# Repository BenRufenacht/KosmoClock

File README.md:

# KosmoClock
 Kosmo Format Clock Module based on LittleBen by Quinie 

Note that the UI varies significantly from Quinie's version.

Status:   
February 2023 - First run of manufacturing found some minor mistakes that were fixed, but the updates to the main board have not been tested.

License:  
[CC-BY-SA](https://creativecommons.org/licenses/by-sa/3.0/)

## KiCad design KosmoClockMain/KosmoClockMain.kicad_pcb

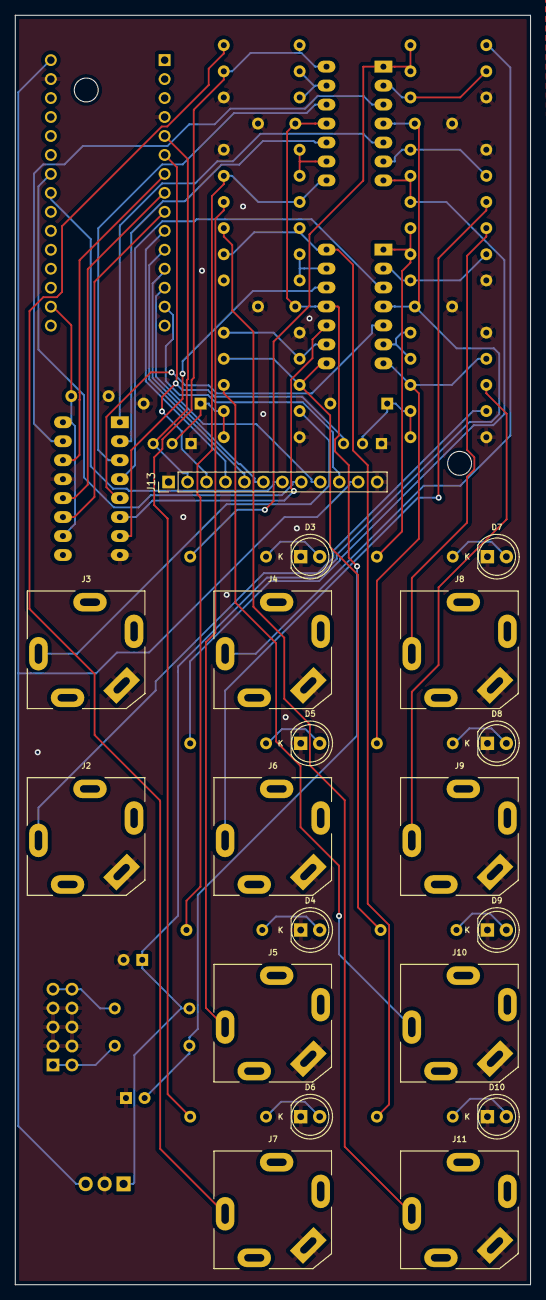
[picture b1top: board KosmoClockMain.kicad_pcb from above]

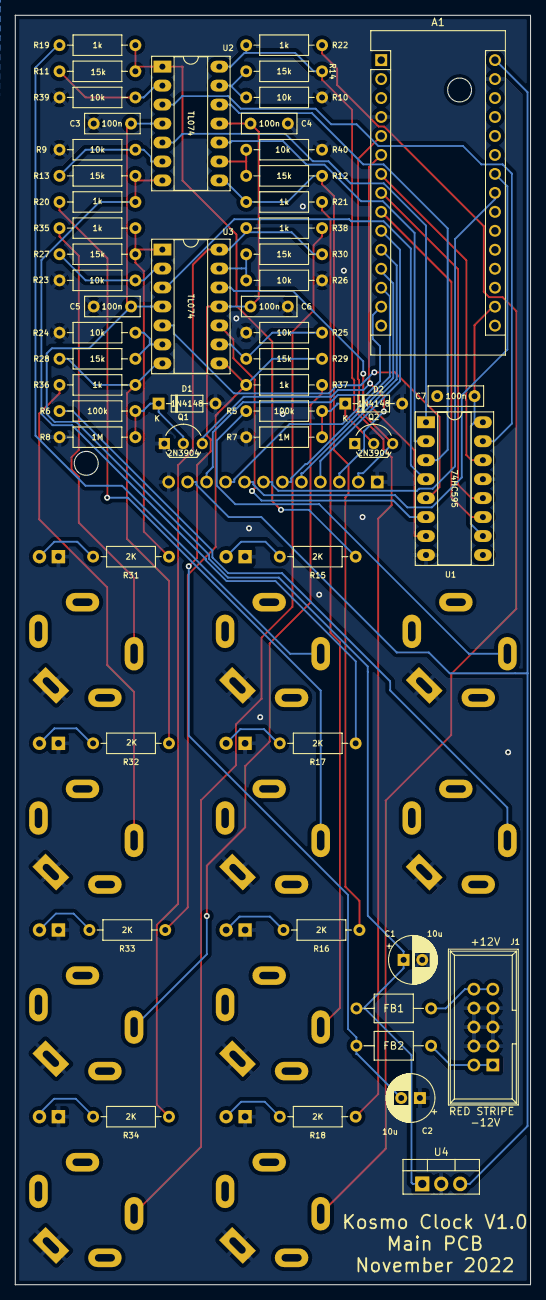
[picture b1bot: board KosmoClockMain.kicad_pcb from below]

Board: 2 copper layers, 69.0 x 170.0 mm, 74 parts (55 on the bottom side), 63 nets.

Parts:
A1: Arduino_Nano_v3.x; Arduino_Nano
C1, C2: 10u; CP_Radial_D6.3mm_P2.50mm
C3, C4, C5, C6, C7: 100n; C_Rect_L7.2mm_W2.5mm_P5.00mm_FKS2_FKP2_MKS2_MKP2
D1, D2: 1N4148; D_DO-35_SOD27_P7.62mm_Horizontal
D3, D4, D5, D6, D7, D8, D9, D10: LED_green; LED_D5.0mm
FB1, FB2: FerriteBead; L_Axial_L5.0mm_D3.6mm_P10.00mm_Horizontal_Murata_BL01RN1A2A2
J1: Synth_power_2x5_passive; Power_Header
J2, J3, J4, J5, J6, J7, J8, J9, J10, J11: AudioJack2; Jack_6.35mm_PJ_629HAN_slots
J13: Conn_01x12; PinHeader_1x12_P2.54mm_Vertical
Q1, Q2: 2N3904; TO-92_Inline_Wide
R5, R6: 100k; R_Axial_DIN0207_L6.3mm_D2.5mm_P10.16mm_Horizontal
R7, R8: 1M; R_Axial_DIN0207_L6.3mm_D2.5mm_P10.16mm_Horizontal
R9, R10, R23, R24, R25, R26, R39, R40: 10k; R_Axial_DIN0207_L6.3mm_D2.5mm_P10.16mm_Horizontal
R11, R12, R13, R14, R27, R28, R29, R30: 15k; R_Axial_DIN0207_L6.3mm_D2.5mm_P10.16mm_Horizontal
R15, R16, R17, R18, R31, R32, R33, R34: 2K; R_Axial_DIN0207_L6.3mm_D2.5mm_P10.16mm_Horizontal
R19, R20, R21, R22, R35, R36, R37, R38: 1k; R_Axial_DIN0207_L6.3mm_D2.5mm_P10.16mm_Horizontal
U1: 74HC595; DIP-16_W7.62mm_Socket_LongPads
U2, U3: TL074; DIP-14_W7.62mm_Socket_LongPads
U4: LM7805_TO220; TO-220-3_Vertical

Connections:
+3V3: A1.17 (3V3), C7.2, U1.10 (~SRCLR), U1.16 (VCC)
+5V: A1.30 (VIN), J13.11, U4.3 (VO)
+12V: C1.1, C3.1, C5.1, FB1.2, U2.4 (V+), U3.4 (V+), U4.1 (VI)
-12V: C2.2, C4.1, C6.1, FB2.2, U2.11 (V-), U3.11 (V-)
/CLOCK: A1.9 (D6), U1.11 (SRCLK)
/DATA: A1.7 (D4), U1.14 (SER)
/ENCA: A1.11 (D8), J13.5
/ENCB: A1.12 (D9), J13.6
/ENCS: A1.10 (D7), J13.4
/LATCH: A1.8 (D5), U1.12 (RCLK)
/OUT1: U1.15 (QA), U2.3 (+)
/OUT2: U1.1 (QB), U2.5 (+)
/OUT3: U1.2 (QC), U2.10 (+)
/OUT4: U1.3 (QD), U2.12 (+)
/OUT5: U1.4 (QE), U3.3 (+)
/OUT6: U1.5 (QF), U3.5 (+)
/OUT7: U1.6 (QG), U3.10 (+)
/OUT8: U1.7 (QH), U3.12 (+)
/SCL: A1.24 (A5), J13.8
/SDA: A1.23 (A4), J13.7
/START: A1.5 (D2), J13.2, Q2.3 (C)
/STARTLED: A1.13 (D10), J13.9
/STOP: A1.6 (D3), J13.3, Q1.3 (C)
/STOPLED: A1.14 (D11), J13.10
GND: A1.4 (GND), A1.29 (GND), C1.2, C2.1, C3.2, C4.2, C5.2, C6.2, C7.1, D1.2 (A), D2.2 (A), D3.1 (K), D4.1 (K), D5.1 (K), D6.1 (K), D7.1 (K), D8.1 (K), D9.1 (K), D10.1 (K), J1.3 (GND), J1.4 (GND), J1.5 (GND), J1.6 (GND), J1.7 (GND), J1.8 (GND), J2.S, J3.S, J4.S, J5.S, J6.S, J7.S, J8.S, J9.S, J10.S, J11.S, J13.1, J13.12, Q1.1 (E), Q2.1 (E), R7.2, R8.2, R9.1, R10.1, R23.1, R24.1, R25.1, R26.1, R39.1, R40.1, U1.8 (GND), U1.13 (~OE), U4.2 (GND)
unnamed: D1.1 (K), Q1.2 (B), R6.2, R8.1
unnamed: D2.1 (K), Q2.2 (B), R5.2, R7.1
unnamed: D3.2 (A), R15.2
unnamed: D4.2 (A), R16.2
unnamed: D5.2 (A), R17.2
unnamed: D6.2 (A), R18.2
unnamed: D7.2 (A), R31.2
unnamed: D8.2 (A), R32.2
unnamed: D9.2 (A), R33.2
unnamed: D10.2 (A), R34.2
unnamed: FB1.1, J1.9 (+12V), J1.10 (+12V)
unnamed: FB2.1, J1.1 (-12V), J1.2 (-12V)
unnamed: J2.T, R6.1
unnamed: J3.T, R5.1
unnamed: J4.T, R19.2
unnamed: J5.T, R21.2
unnamed: J6.T, R20.2
unnamed: J7.T, R22.2
unnamed: J8.T, R35.2
unnamed: J9.T, R36.2
unnamed: J10.T, R37.2
unnamed: J11.T, R38.2
unnamed: R10.2, R14.1, U2.13 (-)
unnamed: R11.1, R39.2, U2.2 (-)
unnamed: R11.2, R15.1, R19.1, U2.1
unnamed: R12.1, R40.2, U2.9 (-)
unnamed: R12.2, R16.1, R21.1, U2.8
unnamed: R9.2, R13.1, U2.6 (-)
unnamed: R13.2, R17.1, R20.1, U2.7
unnamed: R14.2, R18.1, R22.1, U2.14
unnamed: R23.2, R27.1, U3.2 (-)
unnamed: R24.2, R28.1, U3.6 (-)
unnamed: R25.2, R29.1, U3.9 (-)
unnamed: R26.2, R30.1, U3.13 (-)
unnamed: R27.2, R31.1, R35.1, U3.1
unnamed: R28.2, R32.1, R36.1, U3.7
unnamed: R29.2, R33.1, R37.1, U3.8
unnamed: R30.2, R34.1, R38.1, U3.14

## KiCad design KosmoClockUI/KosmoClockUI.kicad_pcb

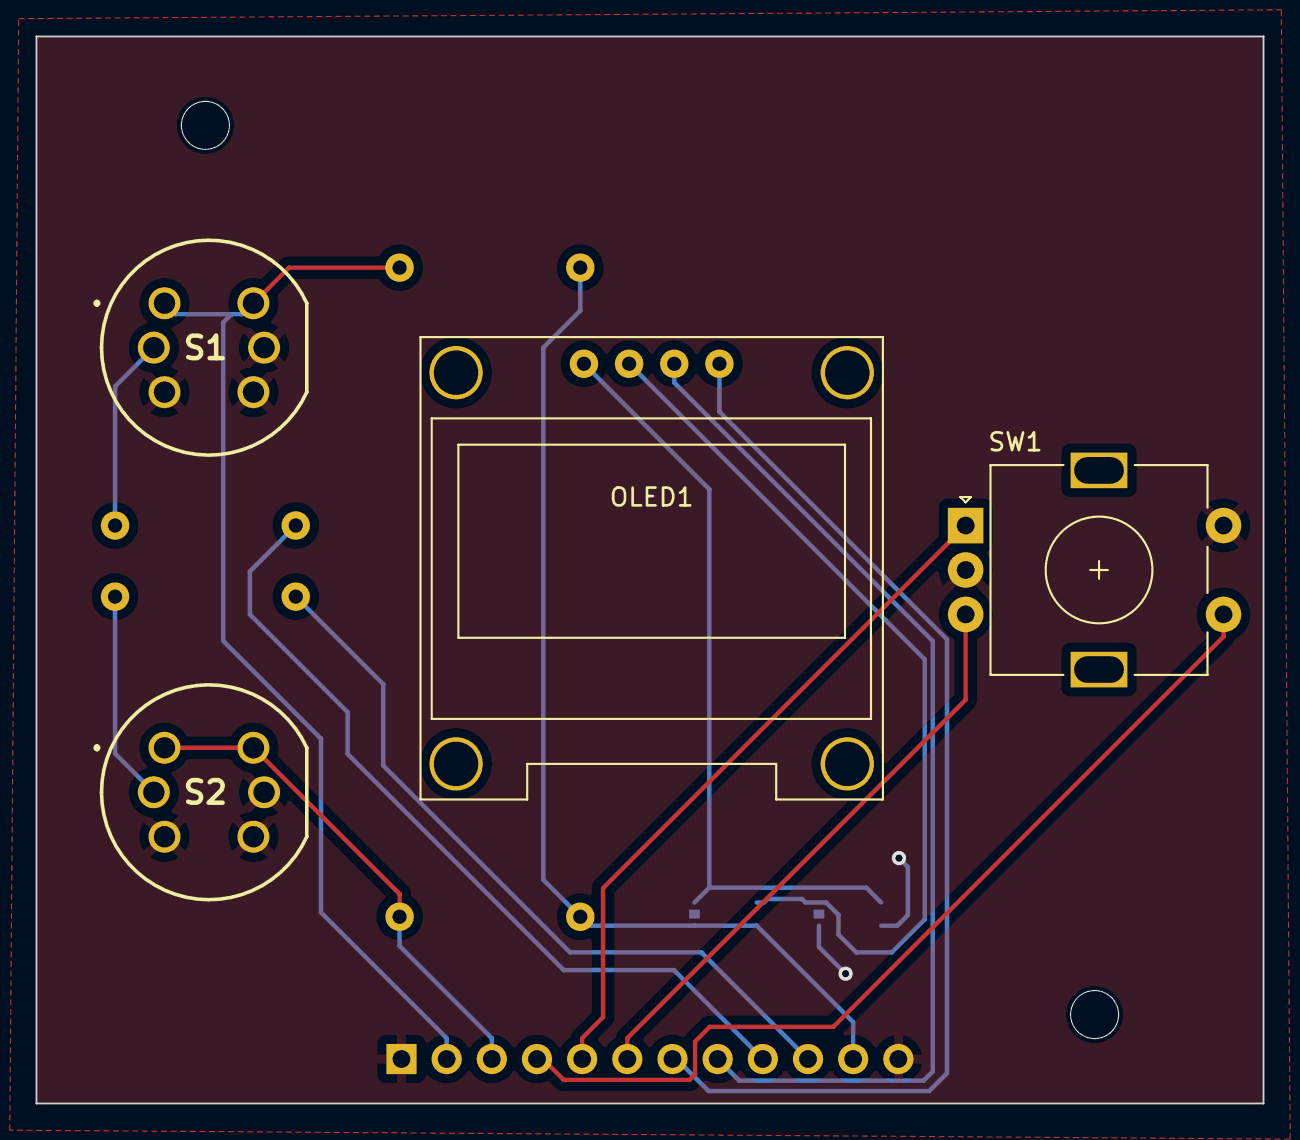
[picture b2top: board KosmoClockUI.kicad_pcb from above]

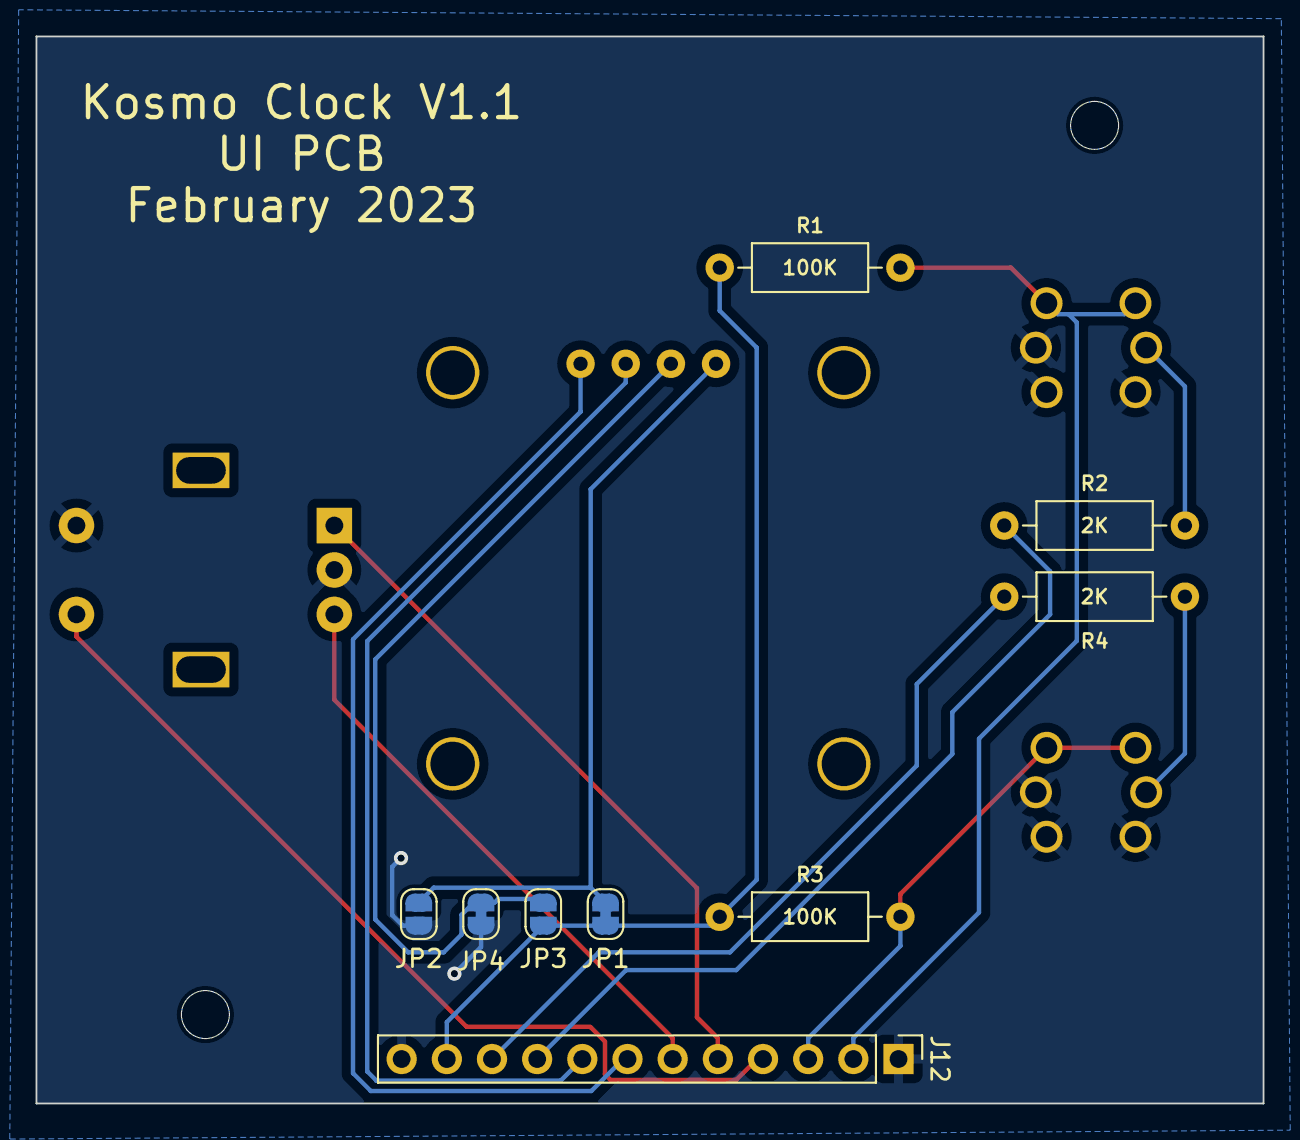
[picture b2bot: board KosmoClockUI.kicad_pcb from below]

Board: 2 copper layers, 69.0 x 60.0 mm, 13 parts (9 on the bottom side), 15 nets.

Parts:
J12: Conn_01x12; PinHeader_1x12_P2.54mm_Vertical
JP1, JP4: JB; SolderJumper-2_P1.3mm_Bridged_RoundedPad1.0x1.5mm
JP2, JP3: JO; SolderJumper-2_P1.3mm_Open_RoundedPad1.0x1.5mm
OLED1: ao_symbols_OLED_128X64; SSD1306_0.96_Oled
R1, R3: 100K; R_Axial_DIN0207_L6.3mm_D2.5mm_P10.16mm_Horizontal
R2, R4: 2K; R_Axial_DIN0207_L6.3mm_D2.5mm_P10.16mm_Horizontal
S1, S2: D6RLGNF1LFS
SW1: RotaryEncoder_Switch; RotaryEncoder_Alps_EC11E-Switch_Vertical_H20mm

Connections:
/5VB: J12.11, JP1.1 (A), JP3.2 (B), R1.1, R3.1
/ENCAB: J12.5, SW1.A
/ENCBB: J12.6, SW1.B
/ENCSB: J12.4, SW1.S1
/GNDB: J12.1, J12.12, JP2.2 (B), JP4.1 (A), S1.3 (NO_1), S1.4 (NO_2), S1.L2 (K), S2.3 (NO_1), S2.4 (NO_2), S2.L2 (K), SW1.C, SW1.S2
/SCLB: J12.8, OLED1.3 (SCL)
/SDAB: J12.7, OLED1.4 (SDA)
/STARTB: J12.2, R1.2, S1.1 (COM_1), S1.2 (COM_2)
/STARTLEDB: J12.9, R2.1
/STOPB: J12.3, R3.2, S2.1 (COM_1), S2.2 (COM_2)
/STOPLEDB: J12.10, R4.1
unnamed: JP1.2 (B), JP2.1 (A), OLED1.1 (VCC)
unnamed: JP3.1 (A), JP4.2 (B), OLED1.2 (GND)
unnamed: R2.2, S1.L1 (A)
unnamed: R4.2, S2.L1 (A)
